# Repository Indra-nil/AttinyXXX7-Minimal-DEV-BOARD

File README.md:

# AttinyXXX7-Minimal-DEV-BOARD

This series dev boards are compatible for tinyAVR 0 Series(Attiny807, Attiny1607), tinyAVR 1 Series(Attiny417, Attiny817, Attiny1617, Attiny3217), tinyAVR 2 Series(Attiny427, Attiny827, Attiny1627, Attiny3227) microcontrollers(VQFN-24).

This is a bare minium pcb. For programing, need any kind of UPDI programmer(jtag2Updi, pyupdi, edbg or atmel ICE) and programs can be written on either Arduino or AVR-GCC.

Some useful links
--------------------

[jtag2updi](https://github.com/ElTangas/jtag2updi.git) 

[pyupdi](https://github.com/mraardvark/pyupdi.git)

[Various UPDI hardwares](https://github.com/wagiminator/AVR-Programmer.git)

[megaTinyCore(arduino core)](https://github.com/SpenceKonde/megaTinyCore.git)

[TinyCore](https://github.com/xukangmin/TinyCore.git)

[Microchip Studio for AVR](https://www.microchip.com/en-us/tools-resources/develop/microchip-studio)

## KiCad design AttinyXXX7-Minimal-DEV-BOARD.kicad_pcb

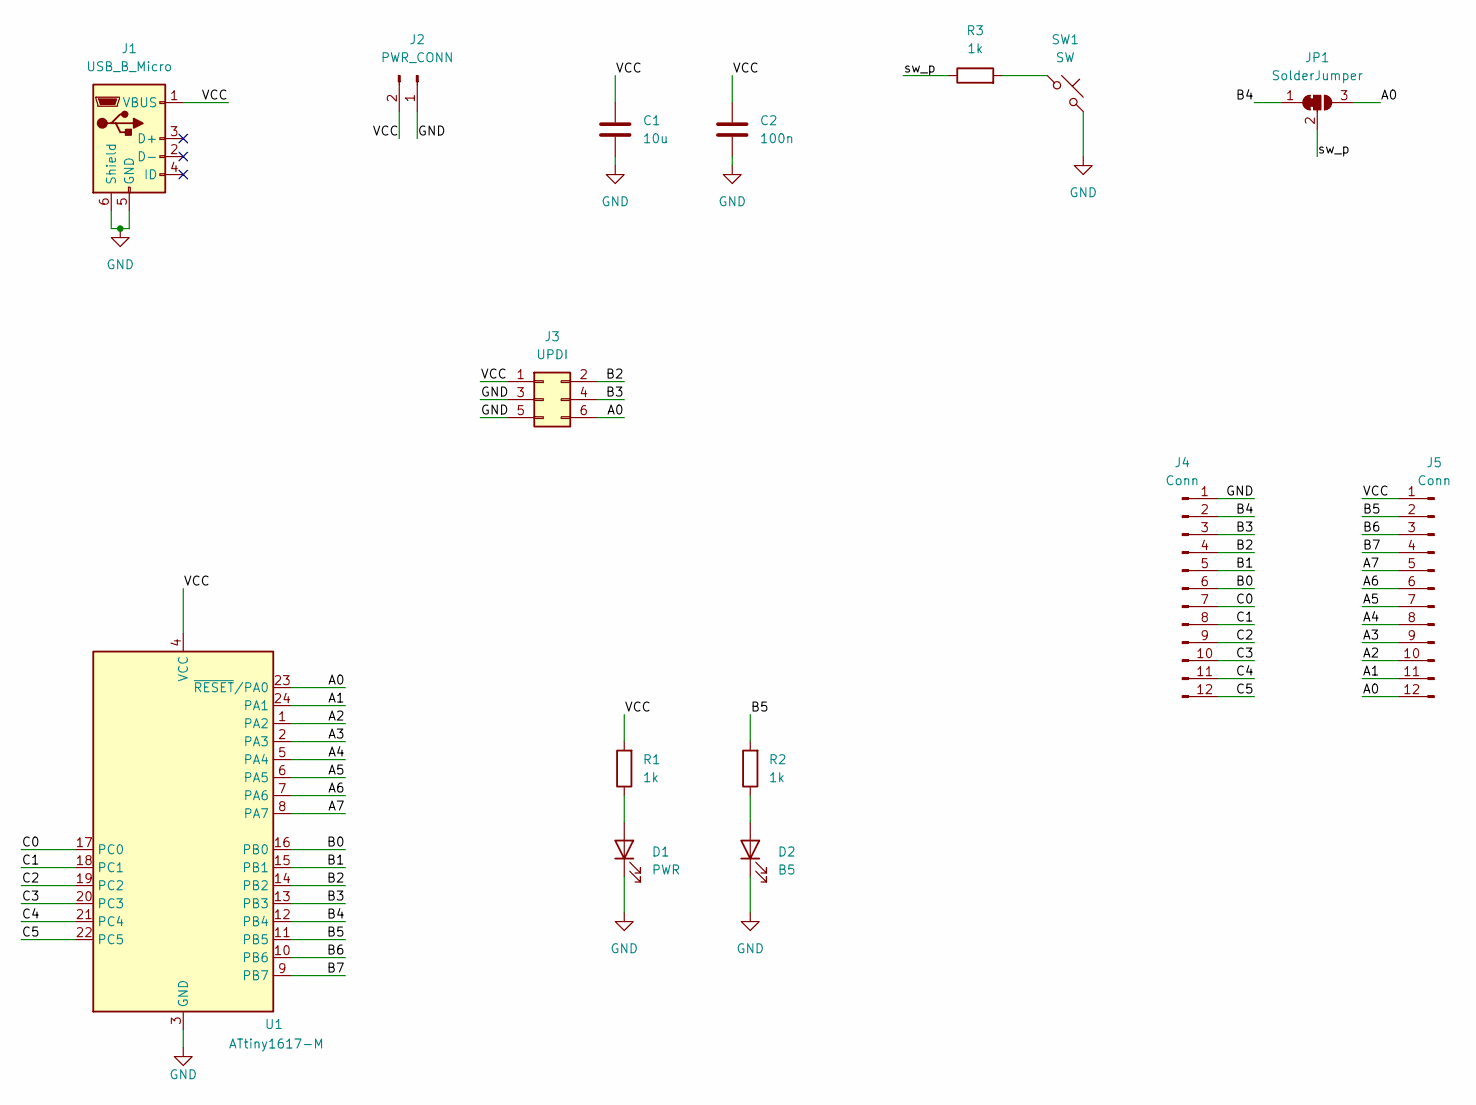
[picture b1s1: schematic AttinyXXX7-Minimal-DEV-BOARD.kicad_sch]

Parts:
C1: 10u; C_0603_1608Metric
C2: 100n; C_0603_1608Metric
D1: PWR; LED_0603_1608Metric
D2: B5; LED_0603_1608Metric
J1: USB_B_Micro; MUP-U513
J2: PWR_CONN; PinHeader_1x02_P2.54mm_Vertical
J3: UPDI; PinHeader_2x03_P2.54mm_Vertical
J4, J5: Conn; PinHeader_1x12_P2.54mm_Vertical
JP1: SolderJumper; SolderJumper-3_P1.3mm_Bridged12_Pad1.0x1.5mm_NumberLabels
R1, R2: 1k; R_0603_1608Metric
R3: 1k; R_0402_1005Metric
SW1: SW; SW_SPST_B3U-1000P
U1: ATtiny1617-M; QFN-24-1EP_4x4mm_P0.5mm_EP2.6x2.6mm

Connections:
/A0: J3.6, J5.12, JP1.3 (B), U1.23 (~RESET/PA0)
/A1: J5.11, U1.24 (PA1)
/A2: J5.10, U1.1 (PA2)
/A3: J5.9, U1.2 (PA3)
/A4: J5.8, U1.5 (PA4)
/A5: J5.7, U1.6 (PA5)
/A6: J5.6, U1.7 (PA6)
/A7: J5.5, U1.8 (PA7)
/B0: J4.6, U1.16 (PB0)
/B1: J4.5, U1.15 (PB1)
/B2: J3.2, J4.4, U1.14 (PB2)
/B3: J3.4, J4.3, U1.13 (PB3)
/B4: J4.2, JP1.1 (A), U1.12 (PB4)
/B5: J5.2, R2.2, U1.11 (PB5)
/B6: J5.3, U1.10 (PB6)
/B7: J5.4, U1.9 (PB7)
/C0: J4.7, U1.17 (PC0)
/C1: J4.8, U1.18 (PC1)
/C2: J4.9, U1.19 (PC2)
/C3: J4.10, U1.20 (PC3)
/C4: J4.11, U1.21 (PC4)
/C5: J4.12, U1.22 (PC5)
/VCC: C1.1, C2.1, J1.1 (VBUS), J2.2, J3.1, J5.1, R1.2, U1.4 (VCC)
/sw_p: JP1.2 (C), R3.1
GND: C1.2, C2.2, D1.1 (K), D2.1 (K), J1.5 (GND), J1.6 (Shield), J2.1, J3.3, J3.5, J4.1, SW1.2, U1.3 (GND), U1.25 (GND)
unnamed: D1.2 (A), R1.1
unnamed: D2.2 (A), R2.1
unnamed: R3.2, SW1.1

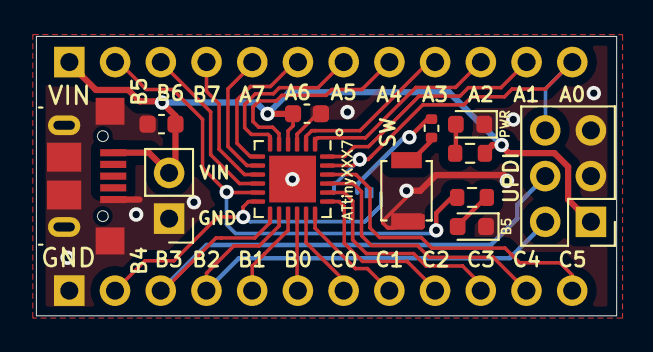
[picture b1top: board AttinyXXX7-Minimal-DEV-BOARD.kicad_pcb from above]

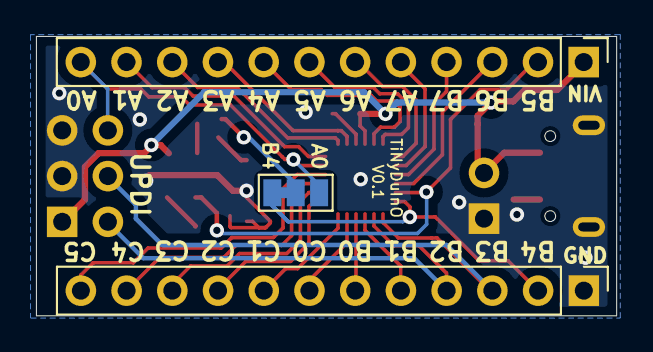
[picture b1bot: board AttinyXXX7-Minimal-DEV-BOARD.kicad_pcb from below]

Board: 2 copper layers, 32.2 x 15.5 mm, 15 parts (3 on the bottom side), 28 nets.

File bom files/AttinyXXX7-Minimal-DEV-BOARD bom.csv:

Ref,Qnty,Value,Cmp name,Footprint,MPN
"C1, ",1,10u,C,Capacitor_SMD:C_0603_1608Metric,CC0603KRX5R6BB106
"C2, ",1,100n,C,Capacitor_SMD:C_0603_1608Metric,CC0603KRX7R9BB104
"D1, ",1,PWR,LED,LED_SMD:LED_0603_1608Metric,19-217/R6C-AL1M2VY/3T 
"D2, ",1,B5,LED,LED_SMD:LED_0603_1608Metric,19-217/G7C-AN1P2/3T
"J1, ",1,USB_B_Micro,USB_B_Micro,MUP-U513:MUP-U513,MUP-U513
"J2, ",1,PWR_CONN,Conn_01x02_Male,Connector_PinHeader_2.54mm:PinHeader_1x02_P2.54mm_Vertical,
"J3, ",1,UPDI,Conn_02x03_Odd_Even,Connector_PinHeader_2.54mm:PinHeader_2x03_P2.54mm_Vertical,
"J4, J5, ",2,Conn,Conn_01x10_Male,Connector_PinHeader_2.54mm:PinHeader_1x10_P2.54mm_Vertical,
"R1, R2, ",2,1k,R,Resistor_SMD:R_0603_1608Metric,RC0603FR-071KL
"R3, ",1,1k,R,Resistor_SMD:R_0402_1005Metric,RC0402JR-071KL
"SW1, ",1,SW,SW_Push_45deg,Button_Switch_SMD:Button_Switch_SMD:SW_SPST_B3U-1000P,B3U-1000P
"U1, ",1,ATtinyXXX7,ATtiny1617-M,Package_DFN_QFN:QFN-24-1EP_4x4mm_P0.5mm_EP2.6x2.6mm,ATTINY1617-MN

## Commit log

2022-05-12 initial release
